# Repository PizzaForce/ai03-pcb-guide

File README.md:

# ai03-pcb-guide
 Getting comfortable with pcb design and git

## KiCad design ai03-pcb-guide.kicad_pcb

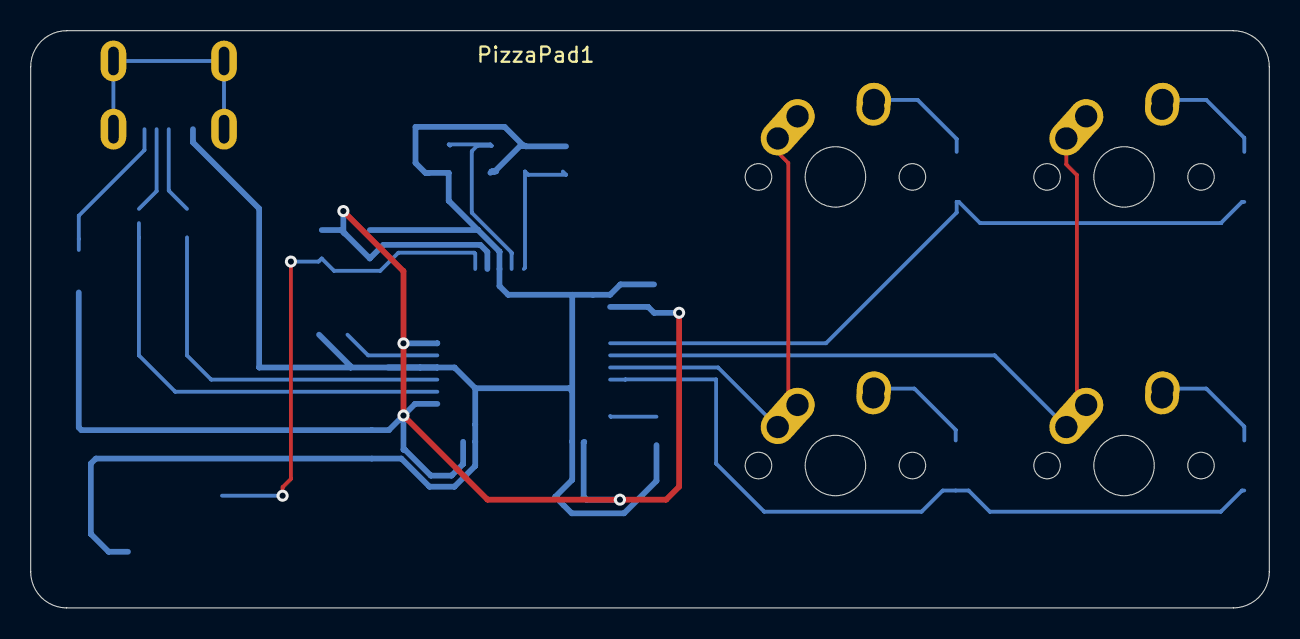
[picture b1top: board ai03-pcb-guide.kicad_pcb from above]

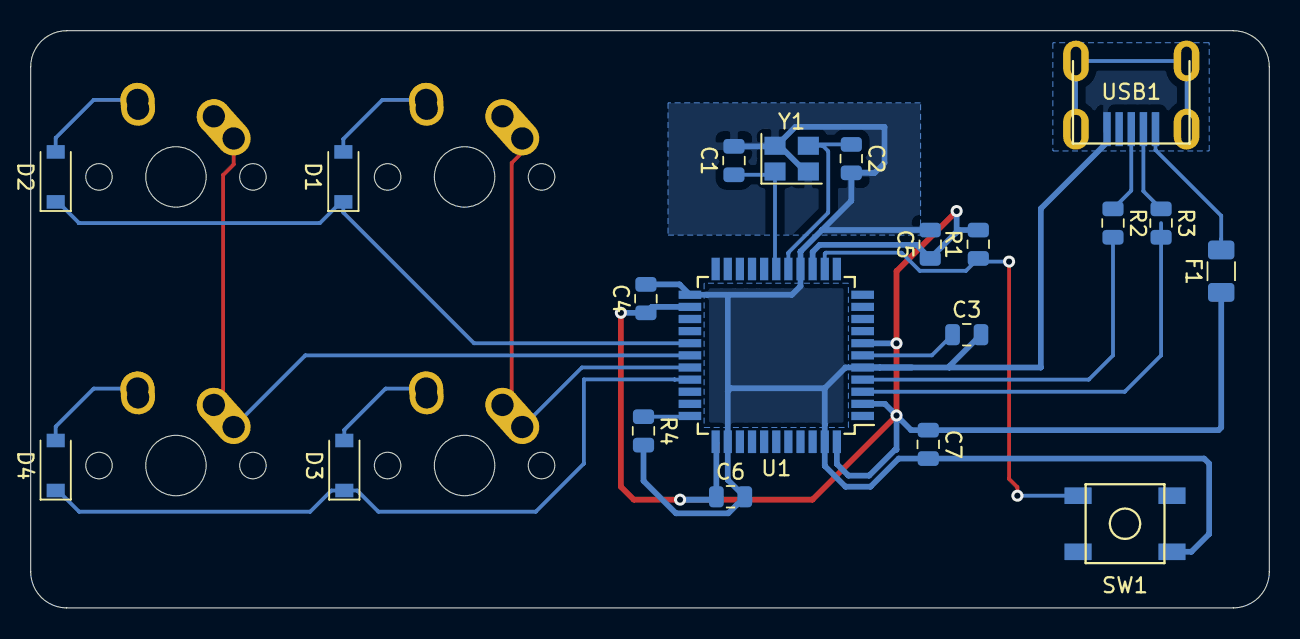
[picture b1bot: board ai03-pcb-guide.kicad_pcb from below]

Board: 2 copper layers, 81.8 x 38.1 mm, 24 parts (20 on the bottom side), 20 nets.

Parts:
C1, C2: 22pF; C_0805_2012Metric
C3: 1uF; C_0805_2012Metric
C4, C5, C6: 0.1uF; C_0805_2012Metric
C7: 10uF; C_0805_2012Metric
D1, D2, D3, D4: D_Small; D_SOD-123
F1: 500mA; Fuse_1206_3216Metric
MX1, MX2, MX3, MX4: MX-NoLED; MX-1U-NoLED
R1, R4: 10k; R_0805_2012Metric
R2, R3: 22; R_0805_2012Metric
SW1: SW_Push; SKQG-1155865
U1: ATmega32U4-AU; TQFP-44_10x10mm_P0.8mm
USB1: Molex-0548190589
Y1: Crystal_GND24_Small; Crystal_SMD_3225-4Pin_3.2x2.5mm

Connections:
+5V: C4.1, C5.1, C6.1, C7.1, F1.1, R1.2, U1.2, U1.7, U1.14, U1.24, U1.34, U1.44
COL0: MX1.1, MX3.1, U1.29
COL1: MX2.1, MX4.1, U1.28
D+: R2.1, USB1.3
D-: R3.1, USB1.4
GND: C1.2, C2.2, C3.2, C4.2, C5.2, C6.2, C7.2, R4.2, SW1.1, U1.5, U1.15, U1.23, U1.35, U1.43, USB1.1, Y1.2, Y1.4
unnamed: C1.1, U1.17, Y1.1
unnamed: C2.1, U1.16, Y1.3
unnamed: C3.1, U1.6
unnamed: D1.2, MX1.2
unnamed: D2.2, MX2.2
unnamed: D3.2, MX3.2
unnamed: D4.2, MX4.2
unnamed: R1.1, SW1.2, U1.13
unnamed: R2.2, U1.4
unnamed: R3.2, U1.3
unnamed: R4.1, U1.33
ROW0: D1.1, D2.1, U1.27
ROW1: D3.1, D4.1, U1.30
VCC: F1.2, USB1.5

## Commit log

2020-10-19 Project Initialize
2020-10-19 Add submodules
2020-10-19 Repo Addition
2020-10-19 Library Changes
2020-10-20 Schematic 1st Pass
2020-10-20 PCB changes
2020-11-07 Kicad edits
2020-11-08 PCB completed
2020-11-08 PCB Design complete
